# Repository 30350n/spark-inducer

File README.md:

### [More info](https://protorack.de/modules/spark-inducer)

### [Support me by buying a Kit at LECTRONZ!](https://lectronz.com/products/spark-inducer)

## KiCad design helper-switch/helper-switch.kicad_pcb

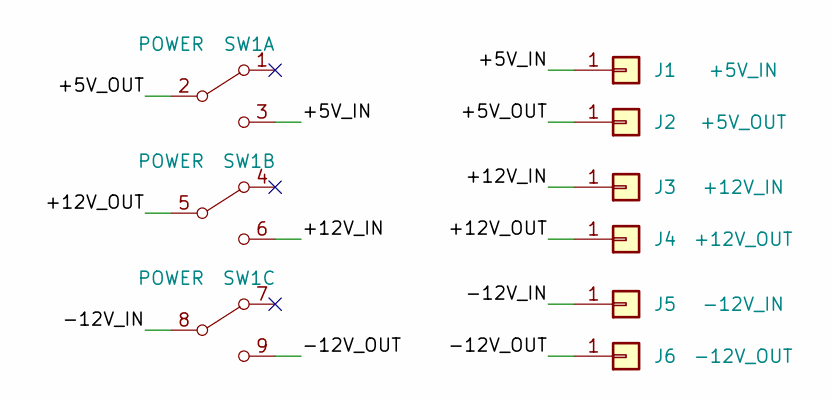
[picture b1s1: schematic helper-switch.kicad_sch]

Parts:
J1: +5V_IN; TestPoint_THTPad_1.8x1.8mm_Drill1.0mm
J2: +5V_OUT; TestPoint_THTPad_1.8x1.8mm_Drill1.0mm
J3: +12V_IN; TestPoint_THTPad_1.8x1.8mm_Drill1.0mm
J4: +12V_OUT; TestPoint_THTPad_1.8x1.8mm_Drill1.0mm
J5: -12V_IN; TestPoint_THTPad_1.8x1.8mm_Drill1.0mm
J6: -12V_OUT; TestPoint_THTPad_1.8x1.8mm_Drill1.0mm
SW1: POWER; CW_GF-161-3011

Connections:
/+5V_IN: J1.1, SW1.3 (C)
/+5V_OUT: J2.1, SW1.2 (B)
/+12V_IN: J3.1, SW1.6 (C)
/+12V_OUT: J4.1, SW1.5 (B)
/-12V_IN: J5.1, SW1.8 (B)
/-12V_OUT: J6.1, SW1.9 (C)

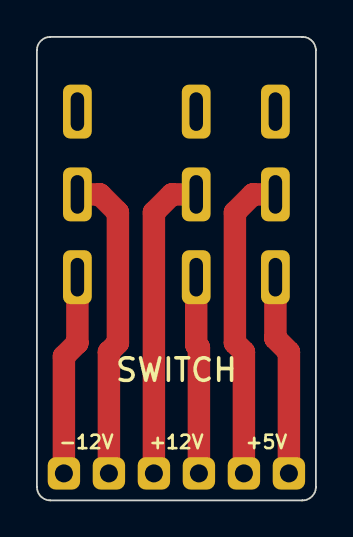
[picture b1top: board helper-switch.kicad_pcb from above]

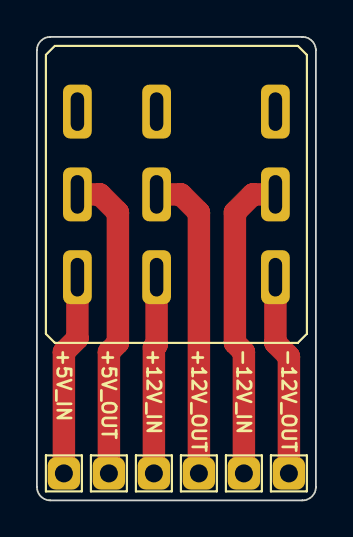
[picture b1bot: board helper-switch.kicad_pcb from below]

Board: 2 copper layers, 15.5 x 25.8 mm, 7 parts (7 on the bottom side), 6 nets.

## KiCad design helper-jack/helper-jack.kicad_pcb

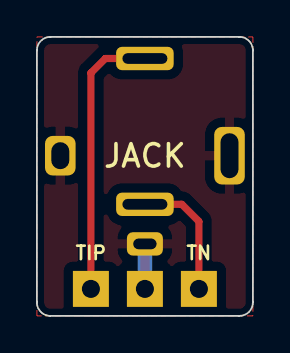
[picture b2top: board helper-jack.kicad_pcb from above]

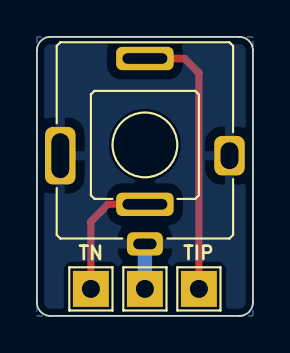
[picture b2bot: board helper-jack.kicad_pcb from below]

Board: 2 copper layers, 12.0 x 15.5 mm, 4 parts (4 on the bottom side), 3 nets.

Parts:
J1: S; TestPoint_THTPad_2.0x2.0mm_Drill1.0mm
J2: TIP; TestPoint_THTPad_2.0x2.0mm_Drill1.0mm
J3: TN; TestPoint_THTPad_2.0x2.0mm_Drill1.0mm
J4: WQP518MA-BM_Combined; QingPu_WQP-WQP518MA-BM_Combined

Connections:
/S: J1.1, J4.S
/T: J2.1, J4.T
/TN: J3.1, J4.TN

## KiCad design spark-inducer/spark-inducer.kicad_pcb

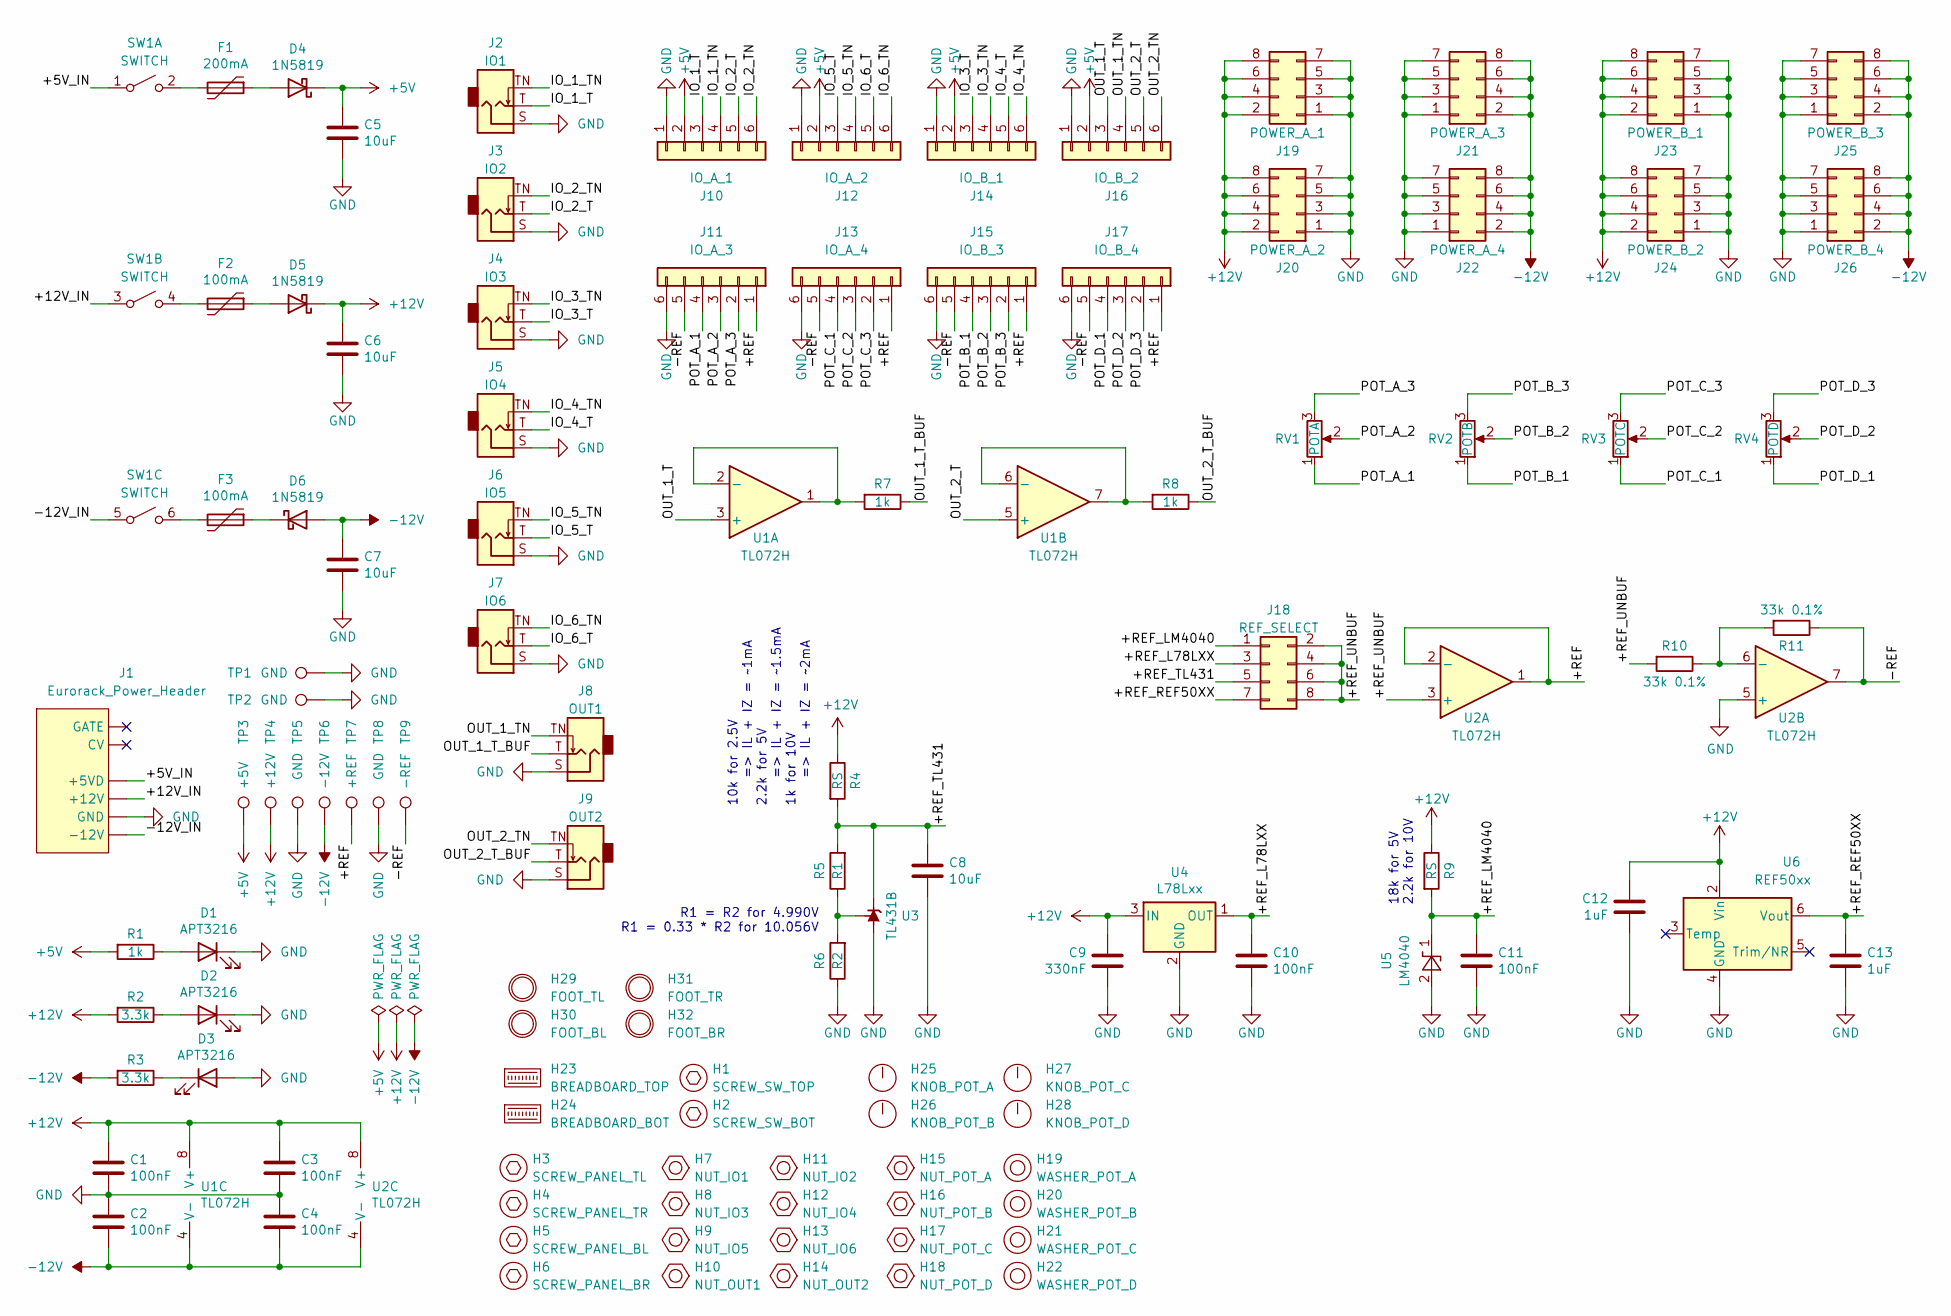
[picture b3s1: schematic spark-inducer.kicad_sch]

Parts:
C1, C2, C3, C4, C10, C11: 100nF; C_0805_2012Metric_Pad1.18x1.45mm_HandSolder
C5, C6, C7, C8: 10uF; C_1206_3216Metric_Pad1.33x1.80mm_HandSolder
C9: 330nF; C_0805_2012Metric_Pad1.18x1.45mm_HandSolder
C12, C13: 1uF; C_0805_2012Metric_Pad1.18x1.45mm_HandSolder
D1, D2, D3: APT3216; LED_1206_3216Metric_ReverseMount_HandSolder
D4, D5, D6: 1N5819; D_SOD-123
F1: 200mA; Fuse_1206_3216Metric_Pad1.42x1.75mm_HandSolder
F2, F3: 100mA; Fuse_1206_3216Metric_Pad1.42x1.75mm_HandSolder
H1: SCREW_SW_TOP; Screw_ISO7380_M2-5x6
H2: SCREW_SW_BOT; Screw_ISO7380_M2-5x6
H3: SCREW_PANEL_TL; Screw_ISO7380_M3x6
H4: SCREW_PANEL_TR; Screw_ISO7380_M3x6
H5: SCREW_PANEL_BL; Screw_ISO7380_M3x6
H6: SCREW_PANEL_BR; Screw_ISO7380_M3x6
H7: NUT_IO1; Nut_M6x2mm_Knurled
H8: NUT_IO3; Nut_M6x2mm_Knurled
H9: NUT_IO5; Nut_M6x2mm_Knurled
H10: NUT_OUT1; Nut_M6x2mm_Knurled
H11: NUT_IO2; Nut_M6x2mm_Knurled
H12: NUT_IO4; Nut_M6x2mm_Knurled
H13: NUT_IO6; Nut_M6x2mm_Knurled
H14: NUT_OUT2; Nut_M6x2mm_Knurled
H15: NUT_POT_A; Nut_M7x2mm_Black
H16: NUT_POT_B; Nut_M7x2mm_Black
H17: NUT_POT_C; Nut_M7x2mm_Black
H18: NUT_POT_D; Nut_M7x2mm_Black
H19: WASHER_POT_A; Washer_RV16AF_2mm_Tab
H20: WASHER_POT_B; Washer_RV16AF_2mm_Tab
H21: WASHER_POT_C; Washer_RV16AF_2mm_Tab
H22: WASHER_POT_D; Washer_RV16AF_2mm_Tab
H23: BREADBOARD_TOP; Breadboard_MB-102
H24: BREADBOARD_BOT; Breadboard_MB-102
H25: KNOB_POT_A; Sifam_3-03-TPN130-006
H26: KNOB_POT_B; Sifam_3-03-TPN130-006
H27: KNOB_POT_C; Sifam_3-03-TPN130-006
H28: KNOB_POT_D; Sifam_3-03-TPN130-006
H29: FOOT_TL; 3M_SJ-5023
H30: FOOT_BL; 3M_SJ-5023
H31: FOOT_TR; 3M_SJ-5023
H32: FOOT_BR; 3M_SJ-5023
J1: Eurorack_Power_Header; Eurorack_Power_Header_2x08_SMD_HandSolder
J2: IO1; QingPu_WQP-WQP518MA-BM_SMD
J3: IO2; QingPu_WQP-WQP518MA-BM_SMD
J4: IO3; QingPu_WQP-WQP518MA-BM_SMD
J5: IO4; QingPu_WQP-WQP518MA-BM_SMD
J6: IO5; QingPu_WQP-WQP518MA-BM_SMD
J7: IO6; QingPu_WQP-WQP518MA-BM_SMD
J8: OUT1; QingPu_WQP-WQP518MA-BM_SMD
J9: OUT2; QingPu_WQP-WQP518MA-BM_SMD
J10: IO_A_1; Samtec_TSW-106-09-T-S-RA_Shortened_SMD
J11: IO_A_3; Samtec_TSW-106-09-T-S-RA_Shortened_SMD
J12: IO_A_2; Samtec_TSW-106-09-T-S-RA_Shortened_SMD
J13: IO_A_4; Samtec_TSW-106-09-T-S-RA_Shortened_SMD
J14: IO_B_1; Samtec_TSW-106-09-T-S-RA_Shortened_SMD
J15: IO_B_3; Samtec_TSW-106-09-T-S-RA_Shortened_SMD
J16: IO_B_2; Samtec_TSW-106-09-T-S-RA_Shortened_SMD
J17: IO_B_4; Samtec_TSW-106-09-T-S-RA_Shortened_SMD
J18: REF_SELECT; PinHeader_2x04_P2.54mm_Vertical_SMD
J19: POWER_A_1; PinHeader_2x04_P2.54mm_Vertical_SMD
J20: POWER_A_2; PinHeader_2x04_P2.54mm_Vertical_SMD
J21: POWER_A_3; PinHeader_2x04_P2.54mm_Vertical_SMD
J22: POWER_A_4; PinHeader_2x04_P2.54mm_Vertical_SMD
J23: POWER_B_1; PinHeader_2x04_P2.54mm_Vertical_SMD
J24: POWER_B_2; PinHeader_2x04_P2.54mm_Vertical_SMD
J25: POWER_B_3; PinHeader_2x04_P2.54mm_Vertical_SMD
J26: POWER_B_4; PinHeader_2x04_P2.54mm_Vertical_SMD
R1, R7, R8: 1k; R_0805_2012Metric_Pad1.20x1.40mm_HandSolder
R2, R3: 3.3k; R_0805_2012Metric_Pad1.20x1.40mm_HandSolder
R4, R9: RS; R_0805_2012Metric_Pad1.20x1.40mm_HandSolder
R5: R1; R_0805_2012Metric_Pad1.20x1.40mm_HandSolder
R6: R2; R_0805_2012Metric_Pad1.20x1.40mm_HandSolder
R10, R11: 33k 0.1%; R_0805_2012Metric_Pad1.20x1.40mm_HandSolder
RV1: POTA; Alpha_RV16AF-10-17K_SMD_Slot
RV2: POTB; Alpha_RV16AF-10-17K_SMD_Slot
RV3: POTC; Alpha_RV16AF-10-17K_SMD_Slot
RV4: POTD; Alpha_RV16AF-10-17K_SMD_Slot
SW1: SWITCH; CW_GF-161-3011_SMD
TP1, TP2: GND; TestPoint_THTPad_D1.5mm_Drill0.7mm
TP3: +5V; TestPoint_Pad_D1.5mm
TP4: +12V; TestPoint_Pad_D1.5mm
TP5, TP8: GND; TestPoint_Pad_D1.5mm
TP6: -12V; TestPoint_Pad_D1.5mm
TP7: +REF; TestPoint_Pad_D1.5mm
TP9: -REF; TestPoint_Pad_D1.5mm
U1, U2: TL072H; SOIC-8_3.9x4.9mm_P1.27mm
U3: TL431B; SOIC-8_3.9x4.9mm_P1.27mm
U4: L78Lxx; SOT-89-3_ThermalReliefs
U5: LM4040; SOT-23
U6: REF50xx; SOIC-8_3.9x4.9mm_P1.27mm

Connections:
+5V: C5.1, D4.1 (K), J10.2, J12.2, J14.2, J16.2, R1.2, TP3.1
+12V: C1.1, C3.1, C6.1, C9.2, C12.2, D5.1 (K), J19.2, J19.4, J19.6, J19.8, J20.2, J20.4, J20.6, J20.8, J23.2, J23.4, J23.6, J23.8, J24.2, J24.4, J24.6, J24.8, R2.2, R4.1, R9.1, TP4.1, U1.8 (V+), U2.8 (V+), U4.3 (IN), U6.2 (Vin)
-12V: C2.2, C4.2, C7.1, D6.2 (A), J21.2, J21.4, J21.6, J21.8, J22.2, J22.4, J22.6, J22.8, J25.2, J25.4, J25.6, J25.8, J26.2, J26.4, J26.6, J26.8, R3.2, TP6.1, U1.4 (V-), U2.4 (V-)
/+5V_IN: J1.+5VD, SW1.1 (A)
/+12V_IN: J1.+12V, SW1.3 (A)
/+REF: J11.1, J13.1, J15.1, J17.1, TP7.1, U2.1, U2.2 (-)
/+REF_L78LXX: C10.2, J18.3, U4.1 (OUT)
/+REF_LM4040: C11.2, J18.1, R9.2, U5.1 (K)
/+REF_REF50XX: C13.2, J18.7, U6.6 (Vout)
/+REF_TL431: C8.2, J18.5, R4.2, R5.2, U3.1 (K)
/+REF_UNBUF: J18.2, J18.4, J18.6, J18.8, R10.2, U2.3 (+)
/-12V_IN: J1.-12V, SW1.5 (A)
/-REF: J11.5, J13.5, J15.5, J17.5, R11.1, TP9.1, U2.7
/IO_1_T: J2.T, J10.3
/IO_1_TN: J2.TN, J10.4
/IO_2_T: J3.T, J10.5
/IO_2_TN: J3.TN, J10.6
/IO_3_T: J4.T, J14.3
/IO_3_TN: J4.TN, J14.4
/IO_4_T: J5.T, J14.5
/IO_4_TN: J5.TN, J14.6
/IO_5_T: J6.T, J12.3
/IO_5_TN: J6.TN, J12.4
/IO_6_T: J7.T, J12.5
/IO_6_TN: J7.TN, J12.6
/OUT_1_T: J16.3, U1.3 (+)
/OUT_1_TN: J8.TN, J16.4
/OUT_1_T_BUF: J8.T, R7.1
/OUT_2_T: J16.5, U1.5 (+)
/OUT_2_TN: J9.TN, J16.6
/OUT_2_T_BUF: J9.T, R8.1
/POT_A_1: J11.4, RV1.1
/POT_A_2: J11.3, RV1.2
/POT_A_3: J11.2, RV1.3
/POT_B_1: J15.4, RV2.1
/POT_B_2: J15.3, RV2.2
/POT_B_3: J15.2, RV2.3
/POT_C_1: J13.4, RV3.1
/POT_C_2: J13.3, RV3.2
/POT_C_3: J13.2, RV3.3
/POT_D_1: J17.4, RV4.1
/POT_D_2: J17.3, RV4.2
/POT_D_3: J17.2, RV4.3
GND: C1.2, C2.1, C3.2, C4.1, C5.2, C6.2, C7.2, C8.1, C9.1, C10.1, C11.1, C12.1, C13.1, D1.1 (K), D2.1 (K), D3.2 (A), J1.GND, J2.S, J3.S, J4.S, J5.S, J6.S, J7.S, J8.S, J9.S, J10.1, J11.6, J12.1, J13.6, J14.1, J15.6, J16.1, J17.6, J19.1, J19.3, J19.5, J19.7, J20.1, J20.3, J20.5, J20.7, J21.1, J21.3, J21.5, J21.7, J22.1, J22.3, J22.5, J22.7, J23.1, J23.3, J23.5, J23.7, J24.1, J24.3, J24.5, J24.7, J25.1, J25.3, J25.5, J25.7, J26.1, J26.3, J26.5, J26.7, R6.1, TP1.1, TP2.1, TP5.1, TP8.1, U2.5 (+), U3.2 (A), U3.3 (A), U3.6 (A), U3.7 (A), U4.2 (GND), U5.2 (A), U6.4 (GND)
unnamed: D1.2 (A), R1.1
unnamed: D2.2 (A), R2.1
unnamed: D3.1 (K), R3.1
unnamed: D4.2 (A), F1.1
unnamed: D5.2 (A), F2.1
unnamed: D6.1 (K), F3.1
unnamed: F1.2, SW1.2 (B)
unnamed: F2.2, SW1.4 (B)
unnamed: F3.2, SW1.6 (B)
unnamed: R7.2, U1.1, U1.2 (-)
unnamed: R8.2, U1.6 (-), U1.7
unnamed: R10.1, R11.2, U2.6 (-)
unnamed: R5.1, R6.2, U3.8 (REF)

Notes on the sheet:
18k for 5V 2.2k for 10V
R1 = R2 for 4.990V R1 = 0.33 * R2 for 10.056V
10k for 2.5V => IL + IZ = ~1mA 2.2k for 5V => IL + IZ = ~1.5mA 1k for 10V => IL + IZ = ~2mA

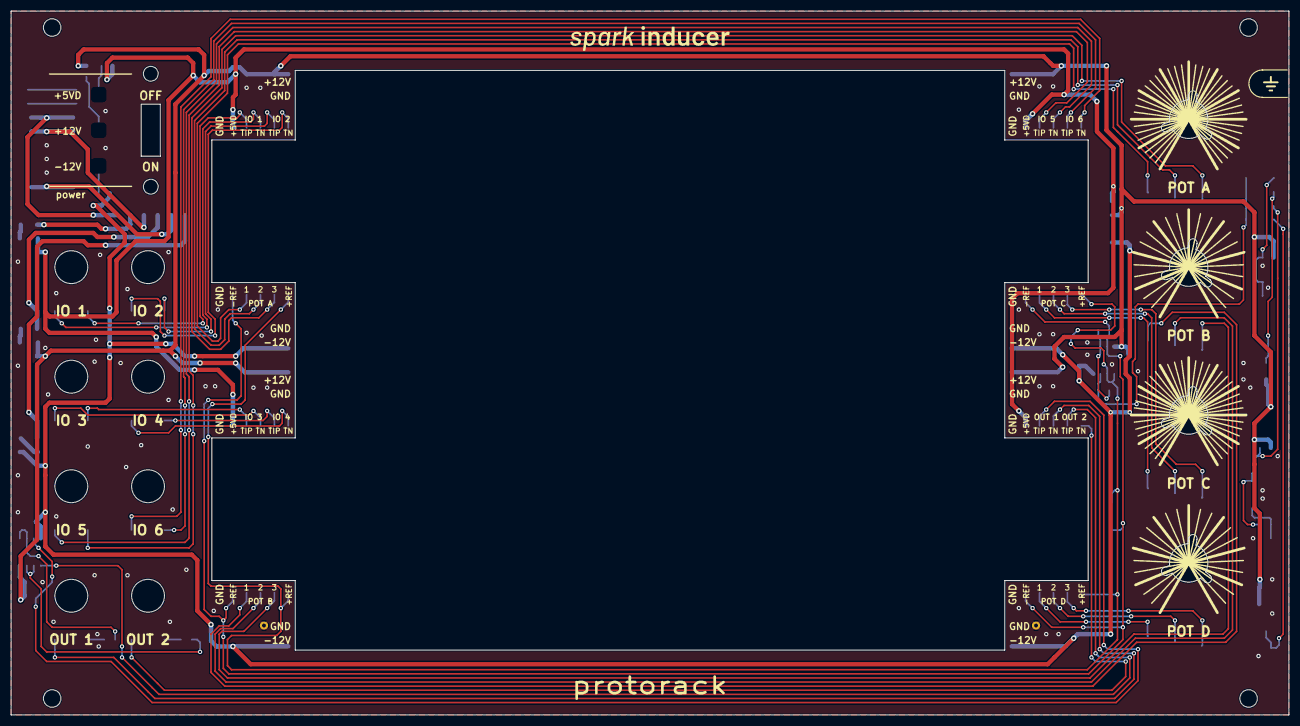
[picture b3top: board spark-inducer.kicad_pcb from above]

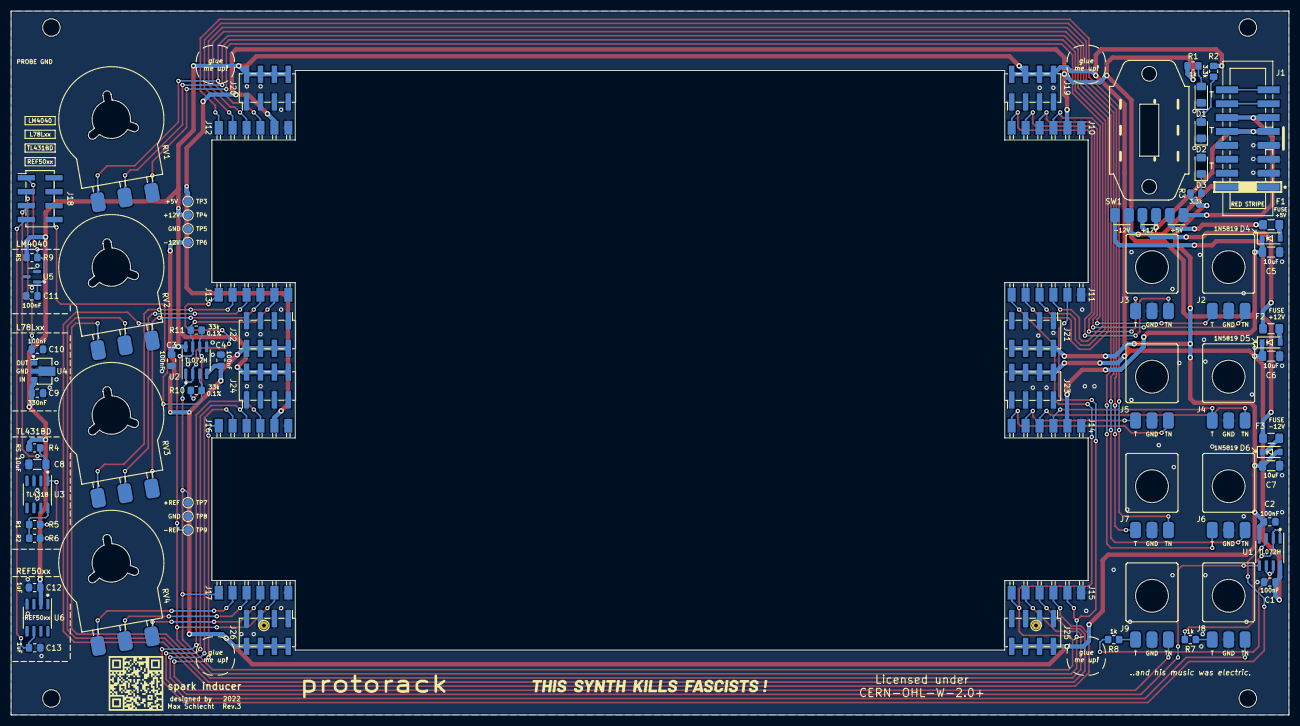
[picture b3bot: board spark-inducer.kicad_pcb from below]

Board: 2 copper layers, 233.2 x 128.4 mm, 116 parts (61 on the bottom side), 57 nets.

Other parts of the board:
Logo: LOGO; Logo_28x6mm
Logo_protorack: Logo_protorack
Logo_spark_inducer: Logo_spark_inducer
QRCode: Val**; QRCode_spark-inducer
TSKF: TSKF_44x4mm

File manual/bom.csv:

Quantity;Reference;Value;Footprint;Manufacturer;PartNumber;SubstituteCriteria;Price per piece (@ qty 100);Price;;;
5;C1, C2, C3, C4, C10;100nF;C_0805_2012Metric_Pad1.18x1.45mm_HandSolder;Samsung Electro-Mechanics;CL21B104KACNNNC;>=25V, X5R/X7R;0.0166;0.083;;;
3;C5, C6, C7;10uF;C_1206_3216Metric_Pad1.42x1.75mm_HandSolder;Samsung Electro-Mechanics;CL31A106KAHNFNE;>=25V, X5R/X7R;0.0815;0.2445;;;
1;C9;330nF;C_0805_2012Metric_Pad1.18x1.45mm_HandSolder;Samsung Electro-Mechanics;CL21B334KBFNNNE;>=25V, X5R/X7R;0.0222;0.0222;;;
3;D1, D2, D3;APT3216;LED_1206_3216Metric_Pad1.42x1.75mm_HandSolder;Kingbright;APT3216SURCK;Red, ~80mcd (TODO);0.1014;0.3042;;;
3;D4, D5, D6;1N5819;D_SOD-123;Diodes Incorporated;1N5819HW-7-F;-;0.1722;0.5166;;;
3;F1, F2, F3;1206L020;Fuse_1206_3216Metric_Pad1.42x1.75mm_HandSolder;Littelfuse Inc.;1206L020YR;TODO;0.2817;0.8451;;;
1;J1;POWER IN;Samtec_HTST-108-01-T-DV;CNC Tech;3020-16-0300-00;-;0.59075;0.59075;;;
8;J2, J3, J4, J5, J6, J7, J8, J9;IO1, IO2, IO3, IO4, IO5, IO6, OUT1, OUT2;QingPu_WQP-PJ376M_SurfaceMount;QingPu;WQP-PJ376M;-;0.2;1.6;;;
8;J10, J11, J12, J13, J14, J15, J16, J17;IO_A_1, IO_A_3, IO_A_2, IO_A_4, IO_B_1, IO_B_3, IO_B_2, IO_B_4;Samtec_TSW-106-09-T-S-RA_Shortened_SurfaceMount;Samtec Inc.;TSW-106-09-T-S-RA;-;0.31;2.48;;;
9;J18, J19, J20, J21, J22, J23, J24, J25, J26;REF_SELECT, POWER_A_1, POWER_A_2, POWER_A_3, POWER_A_4, POWER_B_1, POWER_B_2, POWER_B_3, POWER_B_4;PinHeader_2x04_P2.54mm_Vertical_SMD;Amphenol ICC;54202-S08-04;-;0.2029;1.8261;;;
3;R1, R7, R8;1k;R_0805_2012Metric_Pad1.20x1.40mm_HandSolder;YAGEO;RC0805FR-7W1KL;>=1/4W, 1%;0.0529;0.1587;;;
2;R2, R3;3.3k;R_0805_2012Metric_Pad1.20x1.40mm_HandSolder;YAGEO;RC0805FR-073K3L;>=1/8W, 1%;0.0149;0.0298;;;
2;R10, R11;18k;R_0805_2012Metric_Pad1.20x1.40mm_HandSolder;YAGEO;RC0805FR-0718KL;>=1/8W, 1%;0.0149;0.0298;;;
4;RV1, RV2, RV3, RV4;POTA, POTB, POTC, POTD;Alpha_RV16AF-20-15F_SurfaceMount_Nut_Knob;Alpha Taiwan;;-;0.5;2;;;
1;SW1;SWITCH;CW_GF-161-3011_SurfaceMount;CW Industries;GF-161-3011;-;1.3181;1.3181;;;
2;U1, U2;TL072B;SOIC-8_3.9x4.9mm_P1.27mm;STMicroelectronics;TL072BIDT;-;0.495;0.99;;;
1;U4;L78LXX;SOT-89-3;STMicroelectronics;L78L05ABUTR;-;0.2864;0.2864;;;
;;;;;;;;13.32525;3.5103;4.9181;4.89685
;;;;;;;;;;;
1;C11;100nF;C_0805_2012Metric_Pad1.18x1.45mm_HandSolder;Samsung Electro-Mechanics;CL21B104KACNNNC;>=25V, X5R/X7R;0.0166;0.0166;;;
1;C8;10uF;C_1206_3216Metric_Pad1.42x1.75mm_HandSolder;Samsung Electro-Mechanics;CL31A106KAHNFNE;>=25V, X5R/X7R;0.0815;0.0815;;;
2;C12, C13;1uF;C_0805_2012Metric_Pad1.18x1.45mm_HandSolder;Samsung Electro-Mechanics;CL21B105KAFNNNG;>=25V, X5R/X7R;0.0292;0.0584;;;
2;R4, R9;RS;R_0805_2012Metric_Pad1.20x1.40mm_HandSolder;YAGEO;RC0805FR;>=1/8W, 1%;;0;;;
1;R5;R1;R_0805_2012Metric_Pad1.20x1.40mm_HandSolder;YAGEO;RC0805FR;>=1/8W, 1%;;0;;;
1;R6;R2;R_0805_2012Metric_Pad1.20x1.40mm_HandSolder;YAGEO;RC0805FR;>=1/8W, 1%;;0;;;
1;U3;TL431B;SOIC-8_3.9x4.9mm_P1.27mm;Texas Instruments;TL431BID;-;0.3324;0.3324;;;
1;U5;LM4040;SOT-23;Microchip Technology;LM4040CYM3-5.0-TR;-;0.2431;0.2431;;;
1;U6;REF50XX;SOIC-8_3.9x4.9mm_P1.27mm;Texas Instruments;REF5050AIDR;-;2.4263;2.4263;;;
;;;;;;;;3.1583;;;

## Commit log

2023-06-04 Add Rev.0 and Rev.1
2023-06-04 Update all footprints, use new custom footprints
2023-06-04 Add switch and jack helpers
2023-06-04 Remove legacy files
2023-06-04 Update to KiCad 6
2023-06-04 Add new logos, Finalize silkscreen
2023-06-04 Update qr code
2023-06-04 Add knobs
2023-06-04 Add manual
2023-06-04 Fix breadboard spacings, Add glue marks
2023-06-04 Add larger margin to copper layer next to led windows
2023-06-04 Update files to KiCad 7, Fix edge clearance, Add more spokes to washers
2023-06-04 Add ground clip attachment point, test points, rubber feet
2023-06-05 Add markings to switch and jack helpers
2023-06-05 Update helper jack to KiCad 7, Adjust markings, jack footprint
2023-06-05 Fix helper jack copper edge clearance for v-cuts
2023-06-05 Update helper switch to KiCad 7, Adjust markings
2023-11-23 Rephrase build steps order warning
2023-11-23 Add LM4040 soldering guide, rephrase L78Lxx section
2023-11-23 Add notes about using alternative voltage references to appendix
2023-11-23 Get rid of apostrophes, clarify switch soldering guide
2023-11-23 Use relsize package to fix small text in TOC
2023-11-23 Disable pdfstring commands to silence warnings
2023-11-23 Bump rev to rev.3, year to 2023
2023-12-02 Remove contractions
2023-12-02 Particularize components (1/4W resistors, 1N5819HW diodes, TL431B)
2023-12-15 Add eye protection to tools list
2023-12-15 Fix LM4040 bias resistor note
2023-12-15 Add more placeholder images to LM4040 section
2023-12-15 Add TL431B, REF50xx assembly sections
2023-12-15 Refactor power headers, testing, potentiometers, breadboards sections
2023-12-15 Add gluing section
2023-12-15 Add extra placeholder pictures for switch section
2023-12-15 Make IDs always start at 1 for each subsection
2023-12-15 Add SMD soldering intro
2023-12-15 Improve formatting (pagebreaks)
2023-12-15 Update manual pdf
2023-12-24 Update component codes, Rename TL072B to TL072H, Fix fuses
2023-12-24 Update all images
2023-12-24 Fix IDs in overview images
2023-12-24 Add final touches
2023-12-24 Update pdf
2023-12-24 Rename manual to assembly_manual
2023-12-24 Add user manual
2023-12-24 Add license
2023-12-24 Add simple README
2023-12-24 Fix README
2023-12-24 Add manual pdf
2024-01-04 Fix user manual metadata, vector graphics (v1), Add flyer
2024-01-11 Update BOM
2024-01-16 Add description column to bom
2024-01-16 Add components for P-02 LFO bag to bom
2024-01-18 Fix assembly_manual name
2024-01-19 Add descriptions to BOM, fix substitution criteria

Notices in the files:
spark-inducer/spark-inducer.kicad_pcb:
Licensed under
CERN-OHL-W-2.0+
